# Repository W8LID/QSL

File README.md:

# QSL
A PCB QSL card that can be used as a cross band repeater.

Introduction

The PCB QSL is a spin on the QSL cards that amateur radio operatrors send to one another to confirm contacts they have made over the air. QSL cards resemble post cards but also have information detailing the contact(s) made between two amateur radio operators.  QSL cards are also similar to post cards in that they often have artwork that can represent where or who they came from.

While first trying out KiCad, I came up with the idea that a PCB would make an interesting card that represents my interests in radio, electronics and micro controllers. The PCB QSL has all of the standard features of a paper QSL with silkscreened fields to fill out with contact info. It is also an unpopulated PCB that can be assembled into a working crossband reapeater.

The main components are an Atmel ATMEGA328 and Doji DRA818 VHF and UHF modules. The ATMEGA328 handles the module I/O and serial communications to configure the modules. A small number of passive components are also required to get up and running.

The Circuit

The original version (black solder mask) can only be assembled into a crossband repeater. Later versions can be used as a repeater, the default configuration, or as a dual band 2m, 70cm FM transceiver. In either configuration the goal was to use the minimum number of components as possible. 

In crossband, the audio out and in from each Dorji module are cross connected. This provides a simple voice repeating functionality. 

I/O control for the modules allows for monitoring the squelch status and can key the PTT of an opposing module. The enabling (PD) and the high and low power level of the modules can be handled by the MCU.

While attempting to keep component count to a minimum, it was decided to use the intrnal oscillator on the ATMEGA328. There are no critical timing needs that require the need for an external oscillator. 

Provisions are made for adding headers for ICSP and FTDI programmers to flash a bootloader and program using the Arduino IDE as if it were any other Arduino dev board.

The RF output of the modules are fed to a low pass filter before ending up at u.FL connectors. 

The dual band transceiver option is currently considered experimental and should be treated as such, feel free to offer feedback.

Programming

I have started sending out cards that are already populated with the MCU and the minimum passives required to make a crossband reapeater, the only components required are the DRA818 V and U modules. On these the ATmega328 has already had the bootloader flashed to them. They have also had the basic sketch that is in this repo uploaded to them to verify the bootloader works. I have also moved away from the breadboard board configuration and have moved to MiniCore instead. It is a an improved solution. Instructions for installing MiniCore with the Arduino IDE can be found here https://github.com/MCUdude/MiniCore#how-to-install

Once installed just configure for the proper hardware. Select Tools > Board > MiniCore > ATmega328. Then select Tools > Clock > Internal 8MHz.

Some cards are equipped with the ATmega328PB. Select the variant that matches the chip on your QSL with Tools > Variant.

From there you can upload your own sketches from the Arduino IDE using the FTDI header J3.

A very simple crossband sketch is provided in this repo. It is setup for 145.725MHz input and 434.00MHz output, these are set by the variables named uplink and downlink. Be sure to check your local bandplan to ensure you’re opertaing in the correct portions of the bands. In all cases, please avoid 145.800-146.000MHz and 435.000-438.000MHz as these are internationally recognized satellite bands. DO NOT underestimate the ability of 0.5-1W of power being able to cause interference to satellites. It should also be noted that other weak signal portions of the bands should be avoided.

The provided sketch is very simple and is intended to show how the modules are configured using AT commands. Pin definitions are there to provide an example of what functions are designed for each GPIO. The main loop is very simple in that it reads the squelch pin status on the input module and keys the output module when a signal is detected.

Programming Issues and Other Considerations

As with other Arduino style boards you will get an error if anything is connected to the hardware UART when attempting to upload a sketch. On the PCB QSL we have the VHF module connected to the hardware UART. There are two options to avoid issues here. You can upload your sketch before soldering your module onto the board. You can also utilize the solderable jumper pads JP5 and JP6. Simply cut the small trace inside the pads to program then use a small bit of solder to reconnect after uploading. There is a possibility this might change on future by using SoftwareSerial for both modules.

The DRA818 datasheet lists the transmit current of the modules is 400mA in low power mode and 700mA in high power. Make sure the power supply you’re using is capable of supplying enough current safely. My FTDI programmer works well enough to transmit in low power mode but your mileage may vary.

There are no other known issues at this time.

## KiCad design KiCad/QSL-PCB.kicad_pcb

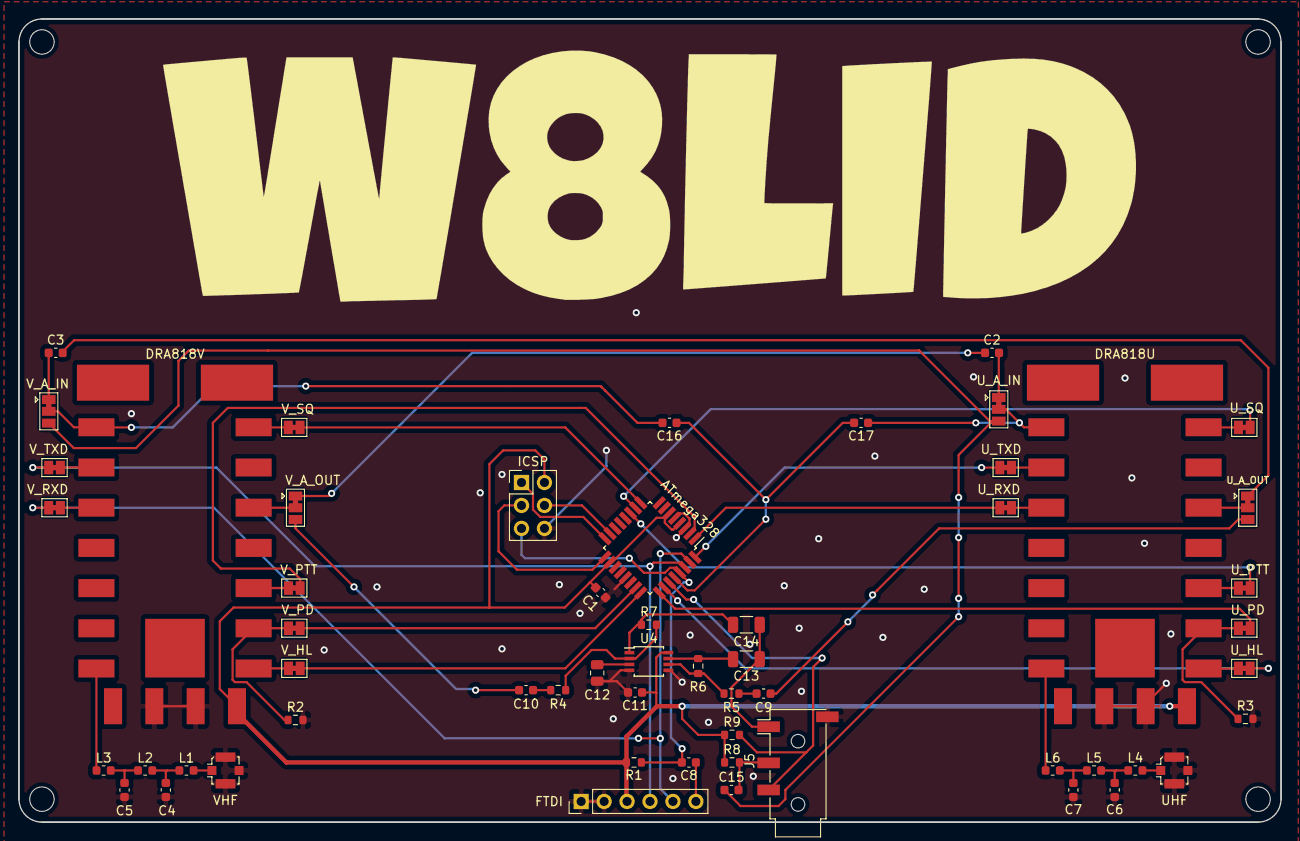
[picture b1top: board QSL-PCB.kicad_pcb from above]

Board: 2 copper layers, 139.7 x 88.9 mm, 57 parts (0 on the bottom side), 61 nets.

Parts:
ATmega328: ATmega328P-AU; TQFP-32_7x7mm_P0.8mm
C1, C8, C15: 100nF; C_0603_1608Metric
C2, C3, C9, C10, C16, C17: 0.47uF; C_0603_1608Metric
C4, C5: 27pF; C_0603_1608Metric
C6, C7: 8.7pF; C_0603_1608Metric
C11: 1uF; C_0603_1608Metric
C12: 4.7uF; R_0805_2012Metric
C13, C14: 100uF; C_1206_3216Metric
FTDI: FTDI; PinHeader_1x06_P2.54mm_Vertical
ICSP: Conn_02x03_Odd_Even; PinHeader_2x03_P2.54mm_Vertical
J5: AudioJack4; Jack_3.5mm_PJ320D_Horizontal
L1, L3: 56nH; L_0603_1608Metric
L2: 100nH; L_0603_1608Metric
L4, L6: 18nH; L_0603_1608Metric
L5: 30nH; L_0603_1608Metric
R1, R2, R3: 10k; R_0603_1608Metric
R4, R5, R6, R7: 20k; R_0603_1608Metric
R8, R9: 10K; R_0603_1608Metric
U2: DRA818V; DRA818
U3: DRA818U; DRA818
U4: LM4810; TSSOP-8_3x3mm_P0.65mm
UHF: UHF; U.FL_Molex_MCRF_73412-0110_Vertical
U_A_IN: SolderJumper_3_Bridged12; SolderJumper-3_P1.3mm_Bridged12_Pad1.0x1.5mm
U_A_OUT: SolderJumper_3_Bridged12; SolderJumper-3_P1.3mm_Bridged12_Pad1.0x1.5mm
U_HL: Jumper; SolderJumper-2_P1.3mm_Bridged_Pad1.0x1.5mm
U_PD: Jumper; SolderJumper-2_P1.3mm_Bridged_Pad1.0x1.5mm
U_PTT: Jumper; SolderJumper-2_P1.3mm_Bridged_Pad1.0x1.5mm
U_RXD: Jumper; SolderJumper-2_P1.3mm_Bridged_Pad1.0x1.5mm
U_SQ: Jumper; SolderJumper-2_P1.3mm_Bridged_Pad1.0x1.5mm
U_TXD: Jumper; SolderJumper-2_P1.3mm_Bridged_Pad1.0x1.5mm
VHF: VHF; U.FL_Molex_MCRF_73412-0110_Vertical
V_A_IN: SolderJumper_3_Bridged12; SolderJumper-3_P1.3mm_Bridged12_Pad1.0x1.5mm
V_A_OUT: SolderJumper_3_Bridged12; SolderJumper-3_P1.3mm_Bridged12_Pad1.0x1.5mm
V_HL: Jumper; SolderJumper-2_P1.3mm_Bridged_Pad1.0x1.5mm
V_PD: Jumper; SolderJumper-2_P1.3mm_Bridged_Pad1.0x1.5mm
V_PTT: Jumper; SolderJumper-2_P1.3mm_Bridged_Pad1.0x1.5mm
V_RXD: Jumper; SolderJumper-2_P1.3mm_Bridged_Pad1.0x1.5mm
V_SQ: Jumper; SolderJumper-2_P1.3mm_Bridged_Pad1.0x1.5mm
V_TXD: Jumper; SolderJumper-2_P1.3mm_Bridged_Pad1.0x1.5mm

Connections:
GND: ATmega328.3, ATmega328.5, ATmega328.21, C1.2, C4.2, C5.2, C6.2, C7.2, C11.2, C12.2, FTDI.1, FTDI.2, ICSP.6, J5.S, R2.2, R3.2, U2.9, U2.10, U3.9, U3.10, U4.4, U4.5, UHF.2, VHF.2
unnamed: C2.1, V_A_OUT.1
unnamed: C2.2, U_A_IN.1
unnamed: C3.1, V_A_IN.1
unnamed: C3.2, U_A_OUT.1
unnamed: C4.1, L1.2, L2.1
unnamed: C5.1, L2.2, L3.1
unnamed: C6.1, L4.2, L5.1
unnamed: C7.1, L5.2, L6.1
unnamed: C8.1, FTDI.6
unnamed: ATmega328.29, C8.2, ICSP.5, R1.2
unnamed: C9.1, R5.2
unnamed: C9.2, U_A_OUT.3
unnamed: C10.1, V_A_OUT.3
unnamed: C10.2, R4.1
unnamed: C12.1, U4.3
unnamed: C13.1, C14.1, J5.T
unnamed: C13.2, R6.1, U4.7
unnamed: C14.2, R7.1, U4.1
unnamed: C15.1, U_A_IN.3, V_A_IN.3
unnamed: C15.2, J5.R1, R8.2
unnamed: ATmega328.28, C16.1, C17.2
unnamed: C16.2, U2.18, V_A_IN.2
unnamed: C17.1, U3.18, U_A_IN.2
unnamed: ATmega328.30, FTDI.4, V_TXD.1
unnamed: ATmega328.31, FTDI.5, V_RXD.1
unnamed: ATmega328.16, ICSP.1
unnamed: ATmega328.17, ICSP.3
unnamed: ATmega328.15, ICSP.4
unnamed: ATmega328.27, J5.R2, R9.2
unnamed: L1.1, VHF.1
unnamed: L3.2, U2.12
unnamed: L4.1, UHF.1
unnamed: L6.2, U3.12
unnamed: R2.1, U2.6, V_PD.2
unnamed: R3.1, U3.6, U_PD.2
unnamed: R4.2, R7.2, U4.2
unnamed: R5.1, R6.2, U4.6
unnamed: ATmega328.1, U_RXD.1
unnamed: ATmega328.2, V_PTT.1
unnamed: ATmega328.9, V_SQ.1
unnamed: ATmega328.10, U_SQ.1
unnamed: ATmega328.11, U_PTT.1
unnamed: ATmega328.23, V_PD.1
unnamed: ATmega328.24, V_HL.1
unnamed: ATmega328.25, U_PD.1
unnamed: ATmega328.26, U_HL.1
unnamed: ATmega328.32, U_TXD.1
unnamed: U2.1, V_SQ.2
unnamed: U2.3, V_A_OUT.2
unnamed: U2.5, V_PTT.2
unnamed: U2.7, V_HL.2
unnamed: U2.16, V_RXD.2
unnamed: U2.17, V_TXD.2
unnamed: U3.1, U_SQ.2
unnamed: U3.3, U_A_OUT.2
unnamed: U3.5, U_PTT.2
unnamed: U3.7, U_HL.2
unnamed: U3.16, U_RXD.2
unnamed: U3.17, U_TXD.2
VCC: ATmega328.4, ATmega328.6, ATmega328.18, C1.1, C11.1, FTDI.3, ICSP.2, R1.1, R8.1, R9.1, U2.8, U3.8, U4.8

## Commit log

2020-12-22 Add PCB layout
    PCB outline layout.
2021-01-13 Initial BOM
    BOM PDF
2021-02-23 Upload sketch
    The sketch that makes it all work
2021-02-23 Board definition
    The breadboard Arduino with internal 8MHz clock is used for this board.
2021-02-25 Update README.md
    Give some actual details
2021-03-07 Delete PCB_QSL.png
    delete to update images
2021-03-07 Update images to latest version
    Use V3 images
2021-03-07 Delete breadboard-1-6-x.zip
    Will no longer use breadboard and use MicroCore instead since its more complete
2021-03-07 Delete BOM.pdf
    delete from here, going into KiCad folder
2021-03-07 Upload KiCad design files
    KiCad files
2021-03-07 Update README.md
    Add image, notes still need updating
2021-03-12 Update README.md
    Move to MiniCore
2021-03-19 Update BOM
    Update BOM spreadsheet and add PDF version.
